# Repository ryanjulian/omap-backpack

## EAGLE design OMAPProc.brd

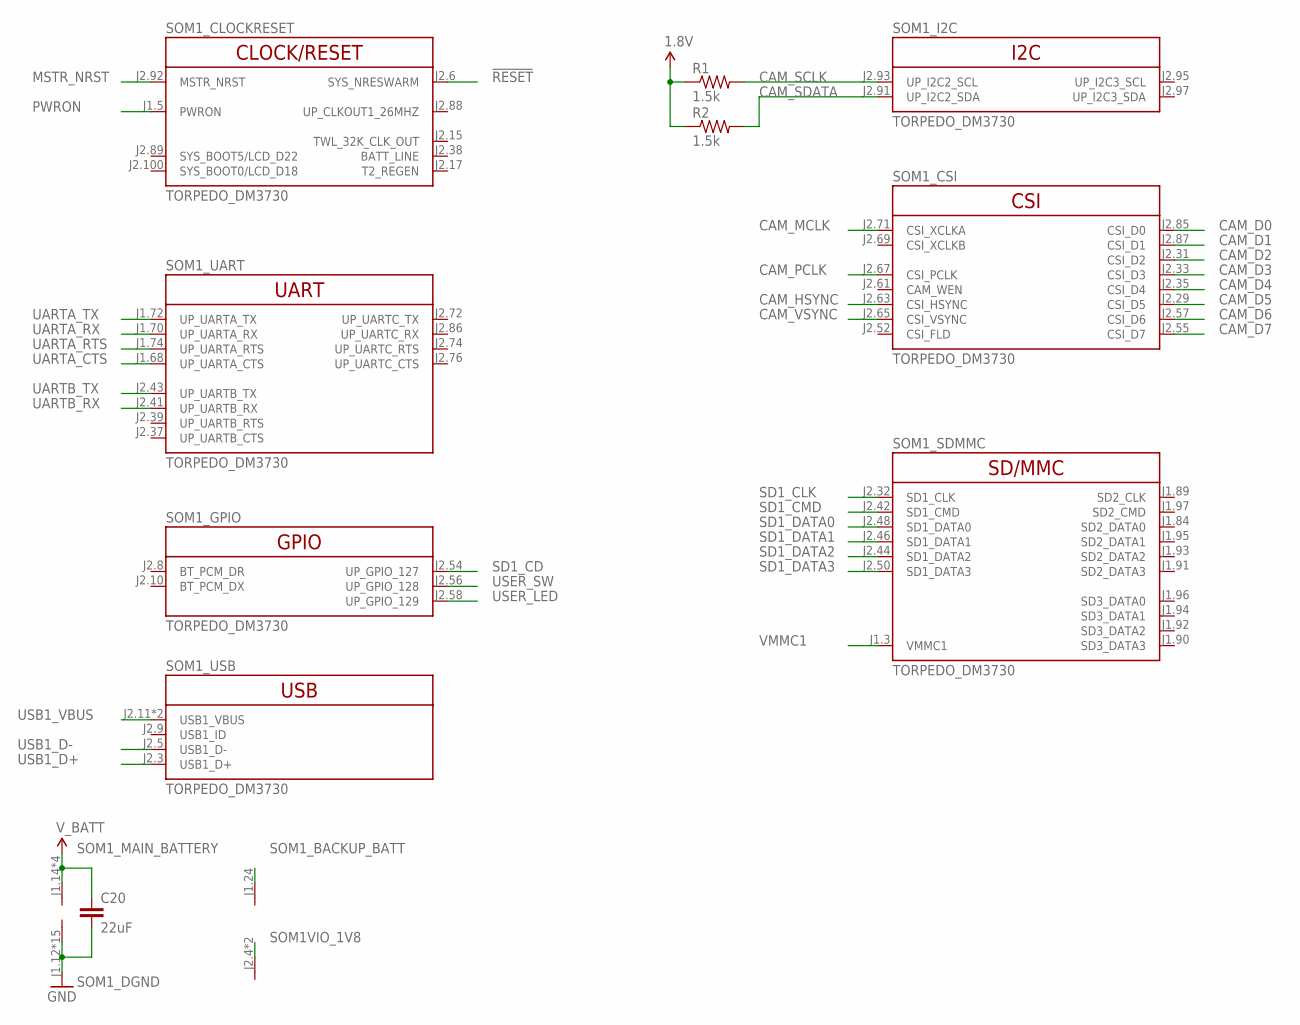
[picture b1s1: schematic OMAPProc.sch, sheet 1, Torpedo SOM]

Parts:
C20: 22uF; 0603-CAP
R1, R2: 1.5k; 0402-RES
SOM1: TORPEDO_DM3730

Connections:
1.8V: R1.1, R2.1; also elsewhere on the board
!RESET: SOM1.J2.6 (SYS_NRESWARM); also elsewhere on the board
CAM_D0: SOM1.J2.85 (CSI_D0); also elsewhere on the board
CAM_D1: SOM1.J2.87 (CSI_D1); also elsewhere on the board
CAM_D2: SOM1.J2.31 (CSI_D2); also elsewhere on the board
CAM_D3: SOM1.J2.33 (CSI_D3); also elsewhere on the board
CAM_D4: SOM1.J2.35 (CSI_D4); also elsewhere on the board
CAM_D5: SOM1.J2.29 (CSI_D5); also elsewhere on the board
CAM_D6: SOM1.J2.57 (CSI_D6); also elsewhere on the board
CAM_D7: SOM1.J2.55 (CSI_D7); also elsewhere on the board
CAM_HSYNC: SOM1.J2.63 (CSI_HSYNC); also elsewhere on the board
CAM_MCLK: SOM1.J2.71 (CSI_XCLKA); also elsewhere on the board
CAM_PCLK: SOM1.J2.67 (CSI_PCLK); also elsewhere on the board
CAM_SCLK: R1.2, SOM1.J2.93 (UP_I2C2_SCL); also elsewhere on the board
CAM_SDATA: R2.2, SOM1.J2.91 (UP_I2C2_SDA); also elsewhere on the board
CAM_VSYNC: SOM1.J2.65 (CSI_VSYNC); also elsewhere on the board
GND: C20.2, SOM1.J1.12 (V-), SOM1.J1.17 (V-), SOM1.J1.22 (V-), SOM1.J1.27 (V-), SOM1.J1.61 (V-), SOM1.J1.85 (V-), SOM1.J1.100 (V-), SOM1.J2.1 (V-), SOM1.J2.2 (V-), SOM1.J2.27 (V-), SOM1.J2.30 (V-), SOM1.J2.59 (V-), SOM1.J2.62 (V-), SOM1.J2.90 (V-), SOM1.J2.99 (V-); also elsewhere on the board
MSTR_NRST: SOM1.J2.92 (MSTR_NRST); also elsewhere on the board
unnamed: SOM1.J2.4 (V+), SOM1.J2.7 (V+)
PWRON: SOM1.J1.5 (PWRON); also elsewhere on the board
SD1_CD: SOM1.J2.54 (UP_GPIO_127); also elsewhere on the board
SD1_CLK: SOM1.J2.32 (SD1_CLK); also elsewhere on the board
SD1_CMD: SOM1.J2.42 (SD1_CMD); also elsewhere on the board
SD1_DATA0: SOM1.J2.48 (SD1_DATA0); also elsewhere on the board
SD1_DATA1: SOM1.J2.46 (SD1_DATA1); also elsewhere on the board
SD1_DATA2: SOM1.J2.44 (SD1_DATA2); also elsewhere on the board
SD1_DATA3: SOM1.J2.50 (SD1_DATA3); also elsewhere on the board
UARTA_CTS: SOM1.J1.68 (UP_UARTA_CTS); also elsewhere on the board
UARTA_RTS: SOM1.J1.74 (UP_UARTA_RTS); also elsewhere on the board
UARTA_RX: SOM1.J1.70 (UP_UARTA_RX); also elsewhere on the board
UARTA_TX: SOM1.J1.72 (UP_UARTA_TX); also elsewhere on the board
UARTB_RX: SOM1.J2.41 (UP_UARTB_RX); also elsewhere on the board
UARTB_TX: SOM1.J2.43 (UP_UARTB_TX); also elsewhere on the board
USB1_D+: SOM1.J2.3 (USB1_D+); also elsewhere on the board
USB1_D-: SOM1.J2.5 (USB1_D-); also elsewhere on the board
USB1_VBUS: SOM1.J2.11 (USB1_VBUS), SOM1.J2.13 (USB1_VBUS); also elsewhere on the board
USER_LED: SOM1.J2.58 (UP_GPIO_129); also elsewhere on the board
USER_SW: SOM1.J2.56 (UP_GPIO_128); also elsewhere on the board
VMMC1: SOM1.J1.3 (VMMC1); also elsewhere on the board
V_BATT: C20.1, SOM1.J1.14 (V+), SOM1.J1.16 (V+), SOM1.J1.18 (V+), SOM1.J1.20 (V+); also elsewhere on the board

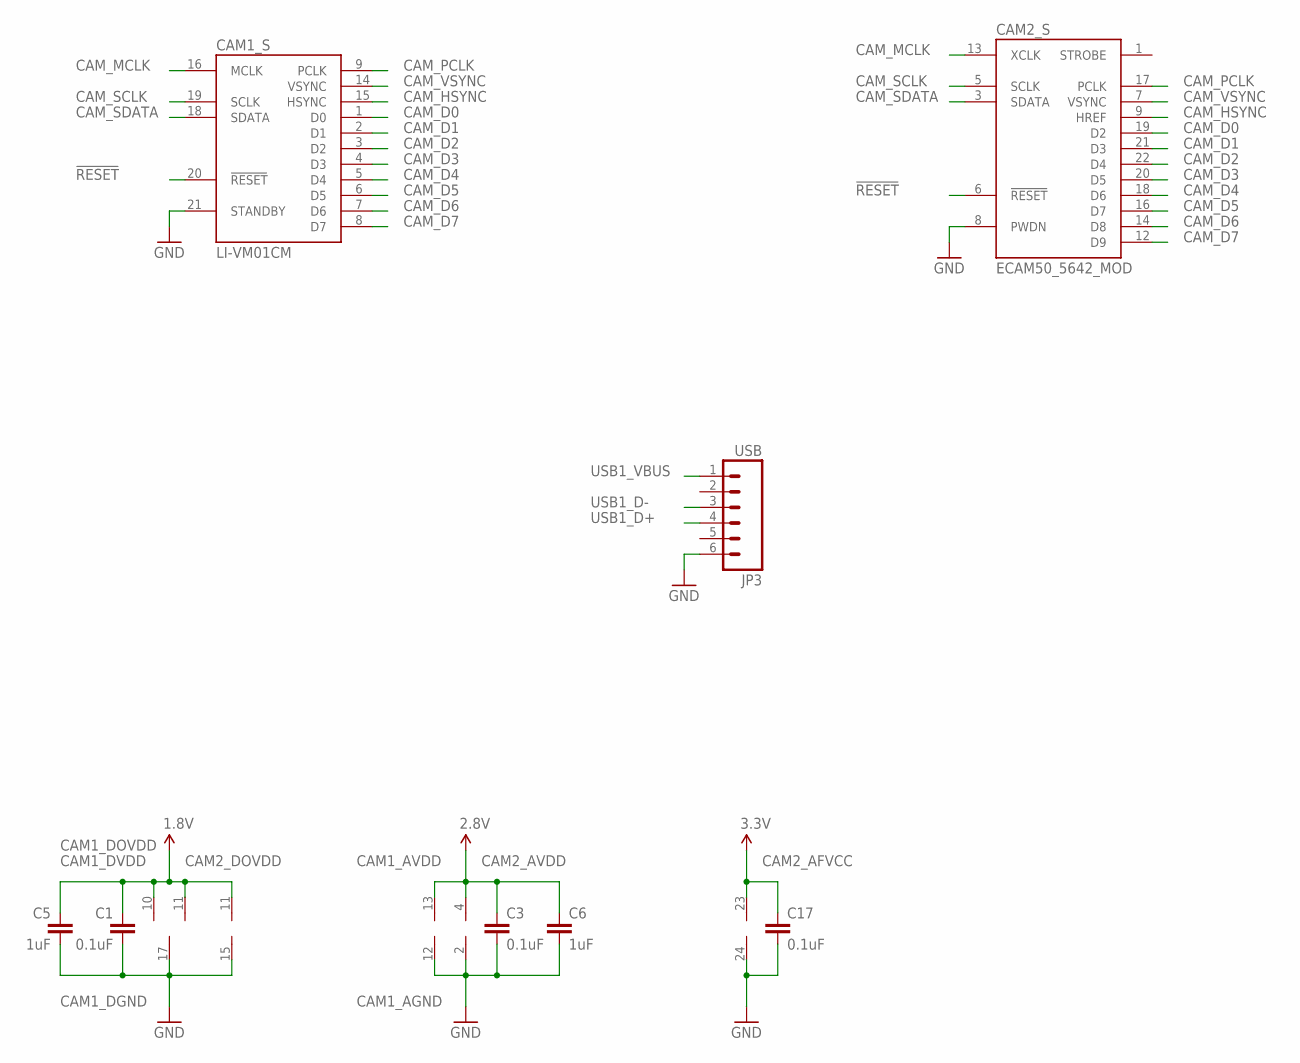
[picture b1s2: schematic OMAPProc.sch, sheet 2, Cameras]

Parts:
C1, C3, C17: 0.1uF; 0402-CAP
C5, C6: 1uF; 0402-CAP
CAM1: LI-VM01CM; AXK7L28227G
CAM2: ECAM50_5642_MOD; XF2W-2415-1A
JP3: USB; MOLEX_503480-0600

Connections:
1.8V: C1.2, C5.2, CAM1.10 (V+), CAM1.11 (V+), CAM2.11 (V+); also elsewhere on the board
2.8V: C3.1, C6.1, CAM1.13 (V+), CAM2.4 (V+); also elsewhere on the board
3.3V: C17.1, CAM2.23 (V+); also elsewhere on the board
!RESET: CAM1.20 (!RESET), CAM2.6 (!RESET); also elsewhere on the board
CAM_D0: CAM1.1 (D0), CAM2.19 (D2); also elsewhere on the board
CAM_D1: CAM1.2 (D1), CAM2.21 (D3); also elsewhere on the board
CAM_D2: CAM1.3 (D2), CAM2.22 (D4); also elsewhere on the board
CAM_D3: CAM1.4 (D3), CAM2.20 (D5); also elsewhere on the board
CAM_D4: CAM1.5 (D4), CAM2.18 (D6); also elsewhere on the board
CAM_D5: CAM1.6 (D5), CAM2.16 (D7); also elsewhere on the board
CAM_D6: CAM1.7 (D6), CAM2.14 (D8); also elsewhere on the board
CAM_D7: CAM1.8 (D7), CAM2.12 (D9); also elsewhere on the board
CAM_HSYNC: CAM1.15 (HSYNC), CAM2.9 (HREF); also elsewhere on the board
CAM_MCLK: CAM1.16 (MCLK), CAM2.13 (XCLK); also elsewhere on the board
CAM_PCLK: CAM1.9 (PCLK), CAM2.17 (PCLK); also elsewhere on the board
CAM_SCLK: CAM1.19 (SCLK), CAM2.5 (SCLK); also elsewhere on the board
CAM_SDATA: CAM1.18 (SDATA), CAM2.3 (SDATA); also elsewhere on the board
CAM_VSYNC: CAM1.14 (VSYNC), CAM2.7 (VSYNC); also elsewhere on the board
GND: C1.1, C3.2, C5.1, C6.2, C17.2, CAM1.12 (V-), CAM1.17 (V-), CAM1.21 (STANDBY), CAM2.2 (V-), CAM2.8 (PWDN), CAM2.15 (V-), CAM2.24 (V-), JP3.6; also elsewhere on the board
USB1_D+: JP3.4; also elsewhere on the board
USB1_D-: JP3.3; also elsewhere on the board
USB1_VBUS: JP3.1; also elsewhere on the board

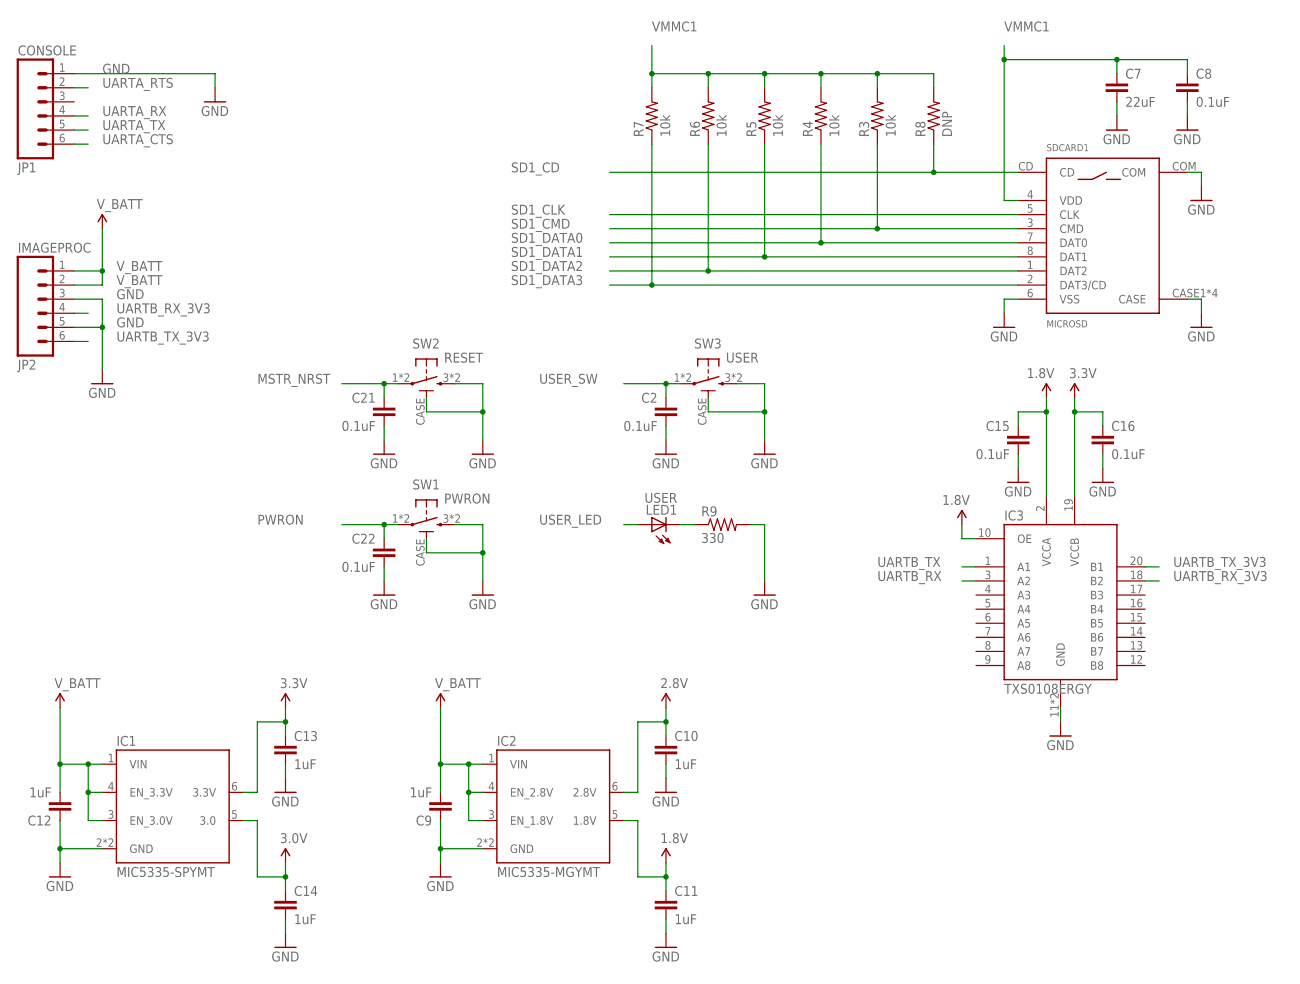
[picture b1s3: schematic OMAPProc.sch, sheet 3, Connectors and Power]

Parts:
C2, C8, C15, C16, C21, C22: 0.1uF; 0402-CAP
C7: 22uF; 0603-CAP
C9, C10, C11, C12, C13, C14: 1uF; 0402-CAP
IC1: MIC5335-SPYMT; MLF-6
IC2: MIC5335-MGYMT; MLF-6
IC3: TXS0108ERGY; R-PVQFN-N20
JP1: CONSOLE; MOLEX_503480-0600
JP2: IMAGEPROC; MOLEX_503480-0600
LED1: USER; LED-0603
R3, R4, R5, R6, R7: 10k; 0402-RES
R8: DNP; 0402-RES
R9: 330; 0402-RES
SDCARD1: MICROSD; AVX_045138008010890+
SW1: PWRON; KMR421G
SW2: RESET; KMR421G
SW3: USER; KMR421G

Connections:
1.8V: C11.1, C15.1, IC2.5 (1.8V), IC3.2 (VCCA), IC3.10 (OE); also elsewhere on the board
2.8V: C10.1, IC2.6 (2.8V); also elsewhere on the board
3.0V: C14.1, IC1.5 (3.0)
3.3V: C13.1, C16.1, IC1.6 (3.3V), IC3.19 (VCCB); also elsewhere on the board
GND: C2.2, C7.2, C8.2, C9.1, C10.2, C11.2, C12.1, C13.2, C14.2, C15.2, C16.2, C21.2, C22.2, IC1.2 (GND), IC1.EPAD (GND), IC2.2 (GND), IC2.EPAD (GND), IC3.11 (GND), IC3.EPAD (GND), JP1.1, JP2.3, JP2.5, R9.2, SDCARD1.6 (VSS), SDCARD1.CASE1 (CASE), SDCARD1.CASE2 (CASE), SDCARD1.CASE3 (CASE), SDCARD1.CASE4 (CASE), SDCARD1.COM, SW1.3 (S), SW1.4 (S), SW1.CASE, SW2.3 (S), SW2.4 (S), SW2.CASE, SW3.3 (S), SW3.4 (S), SW3.CASE; also elsewhere on the board
MSTR_NRST: C21.1, SW2.1, SW2.2; also elsewhere on the board
unnamed: LED1.C, R9.1
PWRON: C22.1, SW1.1, SW1.2; also elsewhere on the board
SD1_CD: R8.1, SDCARD1.CD; also elsewhere on the board
SD1_CLK: SDCARD1.5 (CLK); also elsewhere on the board
SD1_CMD: R3.1, SDCARD1.3 (CMD); also elsewhere on the board
SD1_DATA0: R4.1, SDCARD1.7 (DAT0); also elsewhere on the board
SD1_DATA1: R5.1, SDCARD1.8 (DAT1); also elsewhere on the board
SD1_DATA2: R6.1, SDCARD1.1 (DAT2); also elsewhere on the board
SD1_DATA3: R7.1, SDCARD1.2 (DAT3/CD); also elsewhere on the board
UARTA_CTS: JP1.6; also elsewhere on the board
UARTA_RTS: JP1.2; also elsewhere on the board
UARTA_RX: JP1.4; also elsewhere on the board
UARTA_TX: JP1.5; also elsewhere on the board
UARTB_RX: IC3.3 (A2); also elsewhere on the board
UARTB_RX_3V3: IC3.18 (B2), JP2.4
UARTB_TX: IC3.1 (A1); also elsewhere on the board
UARTB_TX_3V3: IC3.20 (B1), JP2.6
USER_LED: LED1.A; also elsewhere on the board
USER_SW: C2.1, SW3.1, SW3.2; also elsewhere on the board
VMMC1: C7.1, C8.1, R3.2, R4.2, R5.2, R6.2, R7.2, R8.2, SDCARD1.4 (VDD); also elsewhere on the board
V_BATT: C9.2, C12.2, IC1.1 (VIN), IC1.3 (EN_3.0V), IC1.4 (EN_3.3V), IC2.1 (VIN), IC2.3 (EN_1.8V), IC2.4 (EN_2.8V), JP2.1, JP2.2; also elsewhere on the board

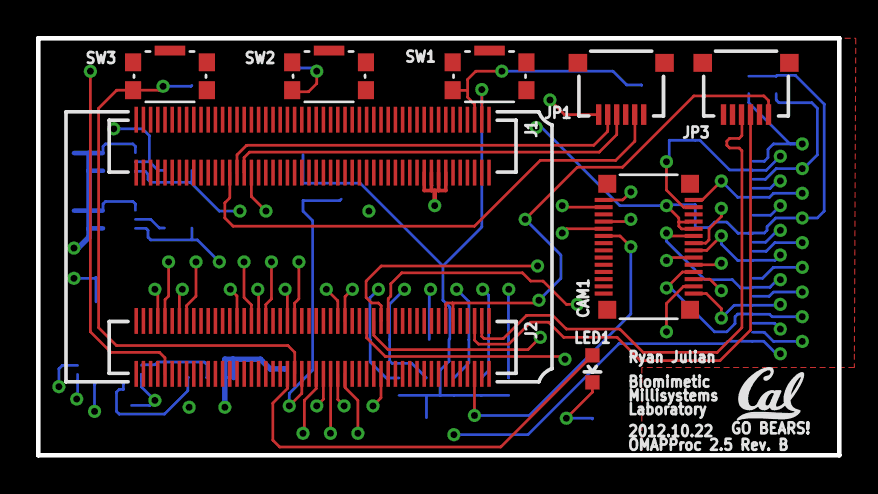
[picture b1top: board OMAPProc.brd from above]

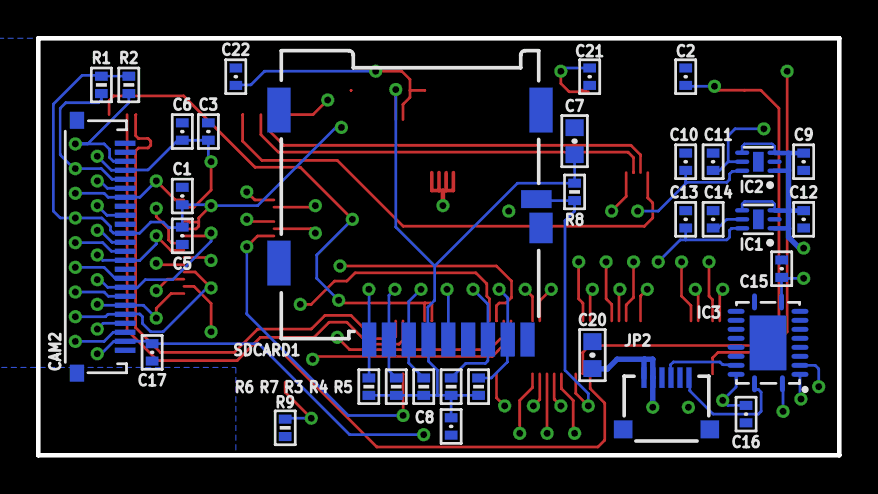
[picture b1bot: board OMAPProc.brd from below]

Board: 4 copper layers, 44.5 x 23.2 mm, 43 parts (34 on the bottom side), 46 nets.

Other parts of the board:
U$12: CAL_LOGO

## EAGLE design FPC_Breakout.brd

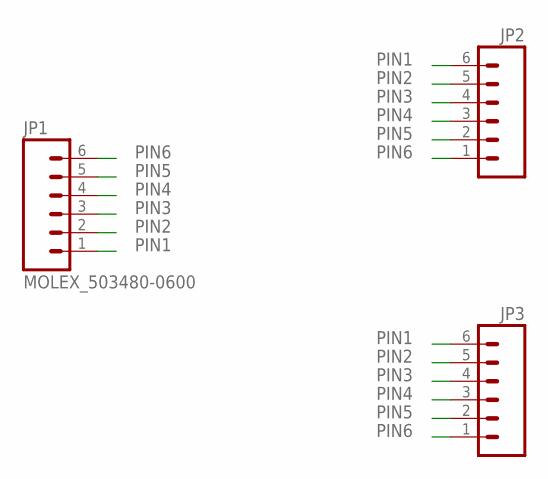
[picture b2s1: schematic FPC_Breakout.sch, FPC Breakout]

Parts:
JP1: MOLEX_503480-0600
JP2: M06SIP_LOCK; 1X06-SIP_LOCK
JP3: M061X06-SMD_EDGE_FEMALE; 1X06-SMD_EDGE

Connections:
PIN1: JP1.1, JP2.6, JP3.6
PIN2: JP1.2, JP2.5, JP3.5
PIN3: JP1.3, JP2.4, JP3.4
PIN4: JP1.4, JP2.3, JP3.3
PIN5: JP1.5, JP2.2, JP3.2
PIN6: JP1.6, JP2.1, JP3.1

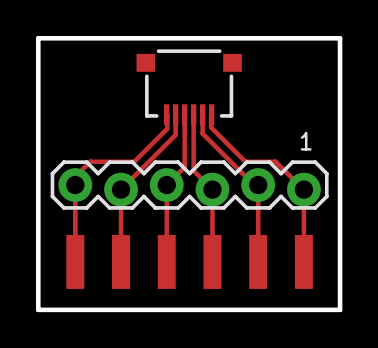
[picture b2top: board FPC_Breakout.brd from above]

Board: 4 copper layers, 16.8 x 15.1 mm, 4 parts (1 on the bottom side), 6 nets.

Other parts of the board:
U$12: CAL_LOGO

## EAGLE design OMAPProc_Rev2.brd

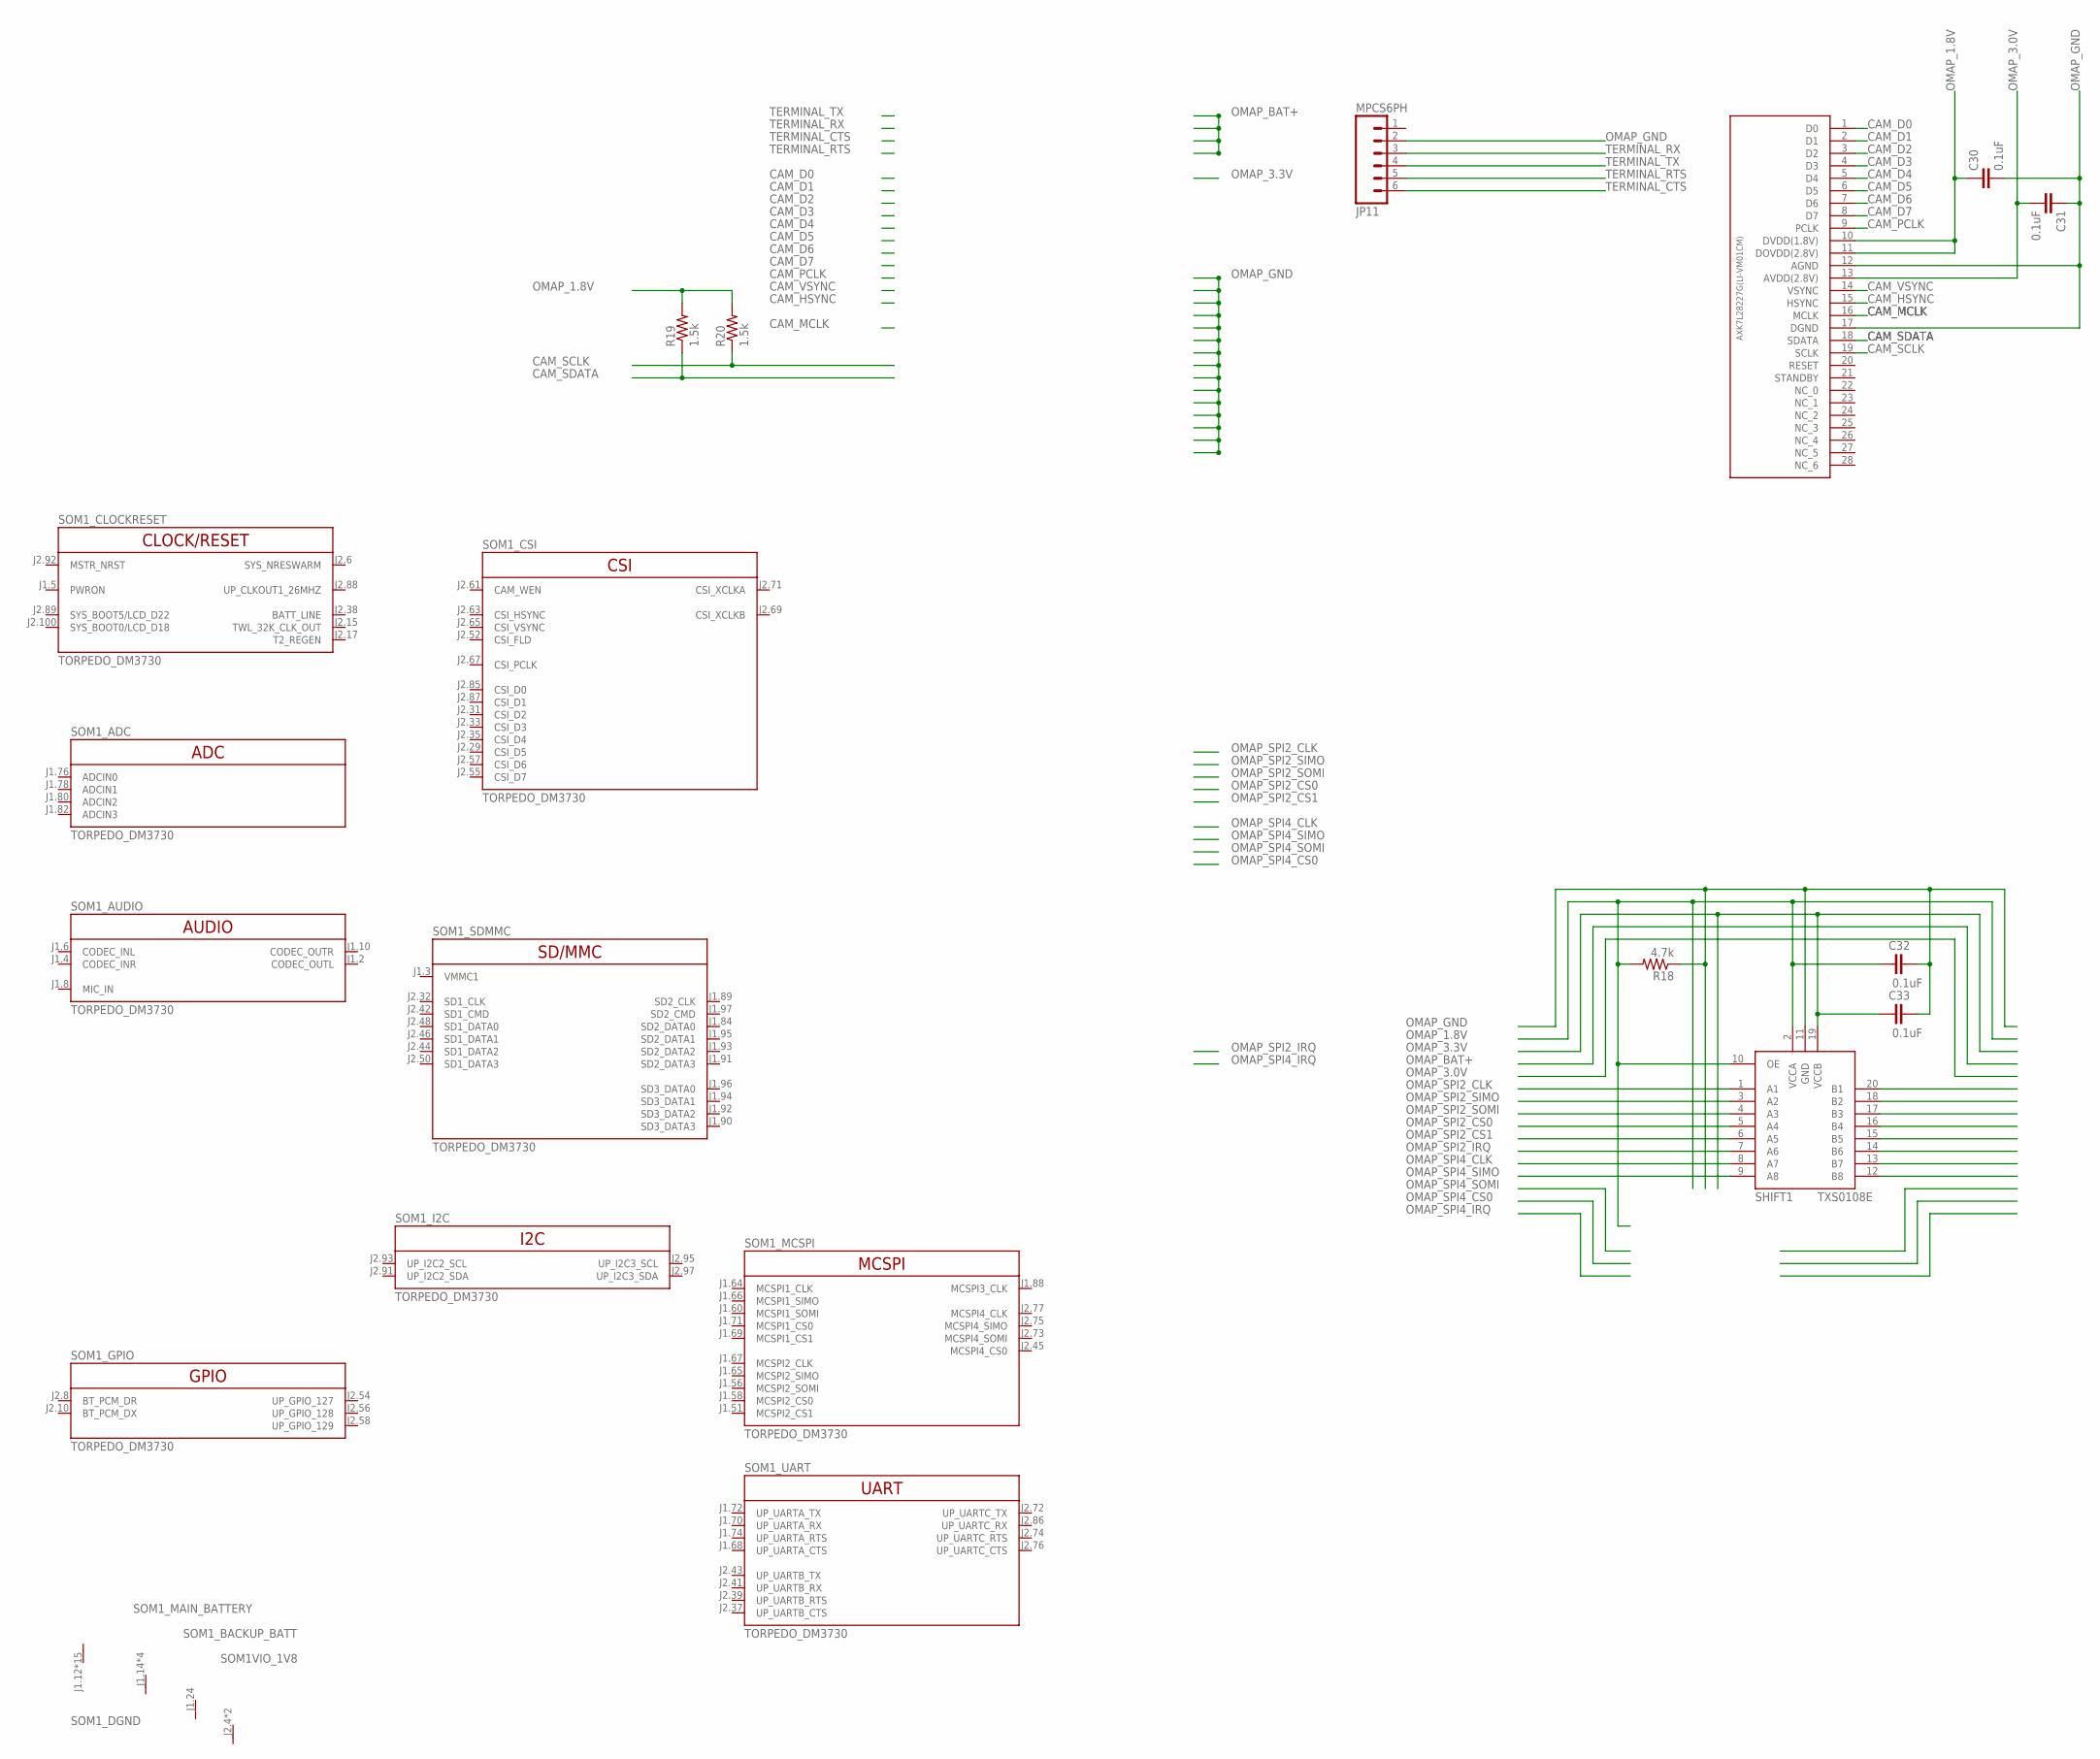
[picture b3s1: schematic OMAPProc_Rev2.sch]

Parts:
C30, C31, C32, C33: 0.1uF; 0402-CAP
CAM1: AXK7L28227G(LI-VM01CM); AXK7L28227G
JP11: MPCS6PH; MOLEX-PICO_CLASP_S6P
R18: 4.7k; R0402
R19, R20: 1.5k; R0402
SHIFT1: TXS0108E; PW_R-PDSO-G20
SOM1: TORPEDO_DM3730

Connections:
CAM_D0: CAM1.1 (D0)
CAM_D1: CAM1.2 (D1)
CAM_D2: CAM1.3 (D2)
CAM_D3: CAM1.4 (D3)
CAM_D4: CAM1.5 (D4)
CAM_D5: CAM1.6 (D5)
CAM_D6: CAM1.7 (D6)
CAM_D7: CAM1.8 (D7)
CAM_HSYNC: CAM1.15 (HSYNC)
CAM_MCLK: CAM1.16 (MCLK)
CAM_PCLK: CAM1.9 (PCLK)
CAM_SCLK: CAM1.19 (SCLK), R20.1
CAM_SDATA: CAM1.18 (SDATA), R19.1
CAM_VSYNC: CAM1.14 (VSYNC)
OMAP_1.8V: C30.1, C32.1, CAM1.10 (DVDD(1.8V)), CAM1.11 (DOVDD(2.8V)), R18.2, R19.2, R20.2, SHIFT1.2 (VCCA), SHIFT1.10 (OE)
OMAP_3.0V: C31.2, CAM1.13 (AVDD(2.8V))
OMAP_3.3V: C33.1, SHIFT1.19 (VCCB)
OMAP_GND: C30.2, C31.1, C32.2, C33.2, CAM1.12 (AGND), CAM1.17 (DGND), JP11.2, R18.1, SHIFT1.11 (GND)
OMAP_SPI2_CLK: SHIFT1.1 (A1)
OMAP_SPI2_CS0: SHIFT1.5 (A4)
OMAP_SPI2_CS1: SHIFT1.6 (A5)
OMAP_SPI2_IRQ: SHIFT1.7 (A6)
OMAP_SPI2_SIMO: SHIFT1.3 (A2)
OMAP_SPI2_SOMI: SHIFT1.4 (A3)
OMAP_SPI4_CLK: SHIFT1.8 (A7)
OMAP_SPI4_SIMO: SHIFT1.9 (A8)
TERMINAL_CTS: JP11.6
TERMINAL_RTS: JP11.5
TERMINAL_RX: JP11.3
TERMINAL_TX: JP11.4
V+: SOM1.J1.14 (V+), SOM1.J1.16 (V+), SOM1.J1.18 (V+), SOM1.J1.20 (V+), SOM1.J1.24 (V+), SOM1.J2.4 (V+), SOM1.J2.7 (V+)
V-: SOM1.J1.12 (V-), SOM1.J1.17 (V-), SOM1.J1.22 (V-), SOM1.J1.27 (V-), SOM1.J1.61 (V-), SOM1.J1.85 (V-), SOM1.J1.100 (V-), SOM1.J2.1 (V-), SOM1.J2.2 (V-), SOM1.J2.27 (V-), SOM1.J2.30 (V-), SOM1.J2.59 (V-), SOM1.J2.62 (V-), SOM1.J2.90 (V-), SOM1.J2.99 (V-)

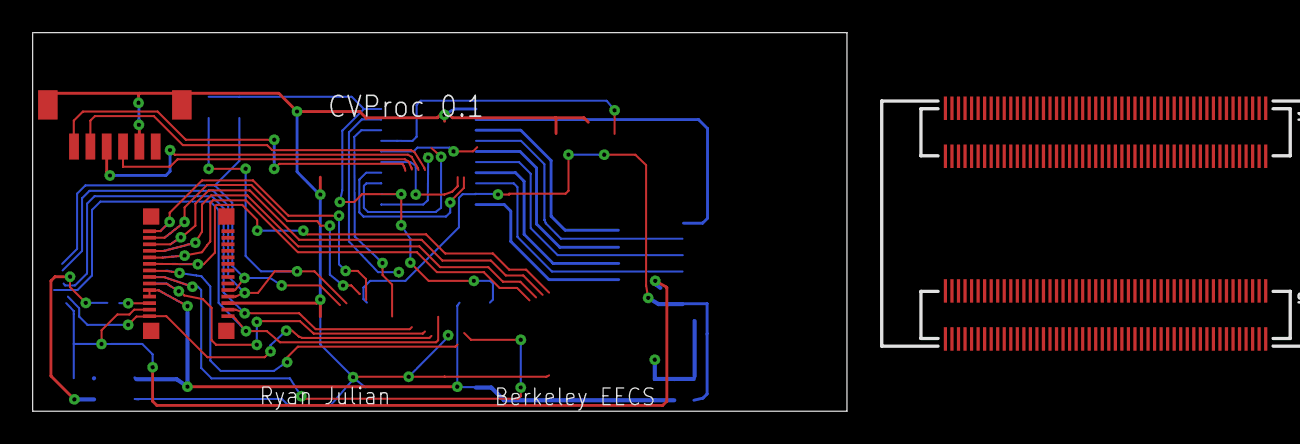
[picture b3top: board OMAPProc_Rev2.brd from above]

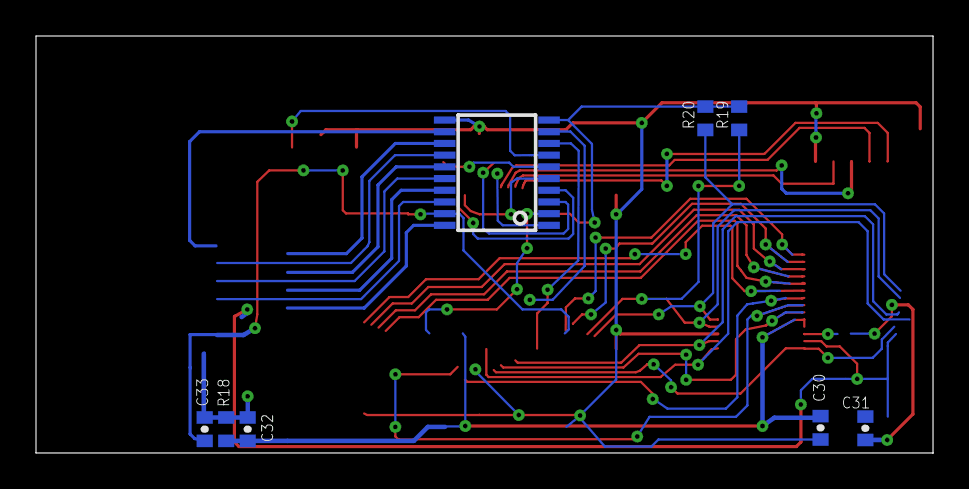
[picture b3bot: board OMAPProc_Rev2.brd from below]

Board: 2 copper layers, 49.8 x 23.2 mm, 11 parts (8 on the bottom side), 8 nets.

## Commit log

2012-07-08 Initial commit.
2012-07-09 Removed old OMAP footprint. Deleted ImageProc and 3M camera connector.
2012-07-09 Removed cam, lbr, and dru folders
2012-07-09 Moved some stuff around.
2012-08-22 Renamed board and schematic
2012-09-20 Pre-reinstall commit
2012-10-05 Near-final placement, partial route
2012-10-05 SD card routing complete
2012-10-08 Routing almost complete
    Missing switches
2012-10-08 Routing and silkscreen complete.
2012-10-09 Add FPC Breakout
2012-10-09 Add ERRATA and README
2012-10-22 Add USB connector

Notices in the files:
parts and their libraries:
SparkFun-Connectors: Licensing: CC v3.0 Share-Alike You are welcome to use this library for commercial purposes.
biomimetic: UC Regents. All rights reserved.
